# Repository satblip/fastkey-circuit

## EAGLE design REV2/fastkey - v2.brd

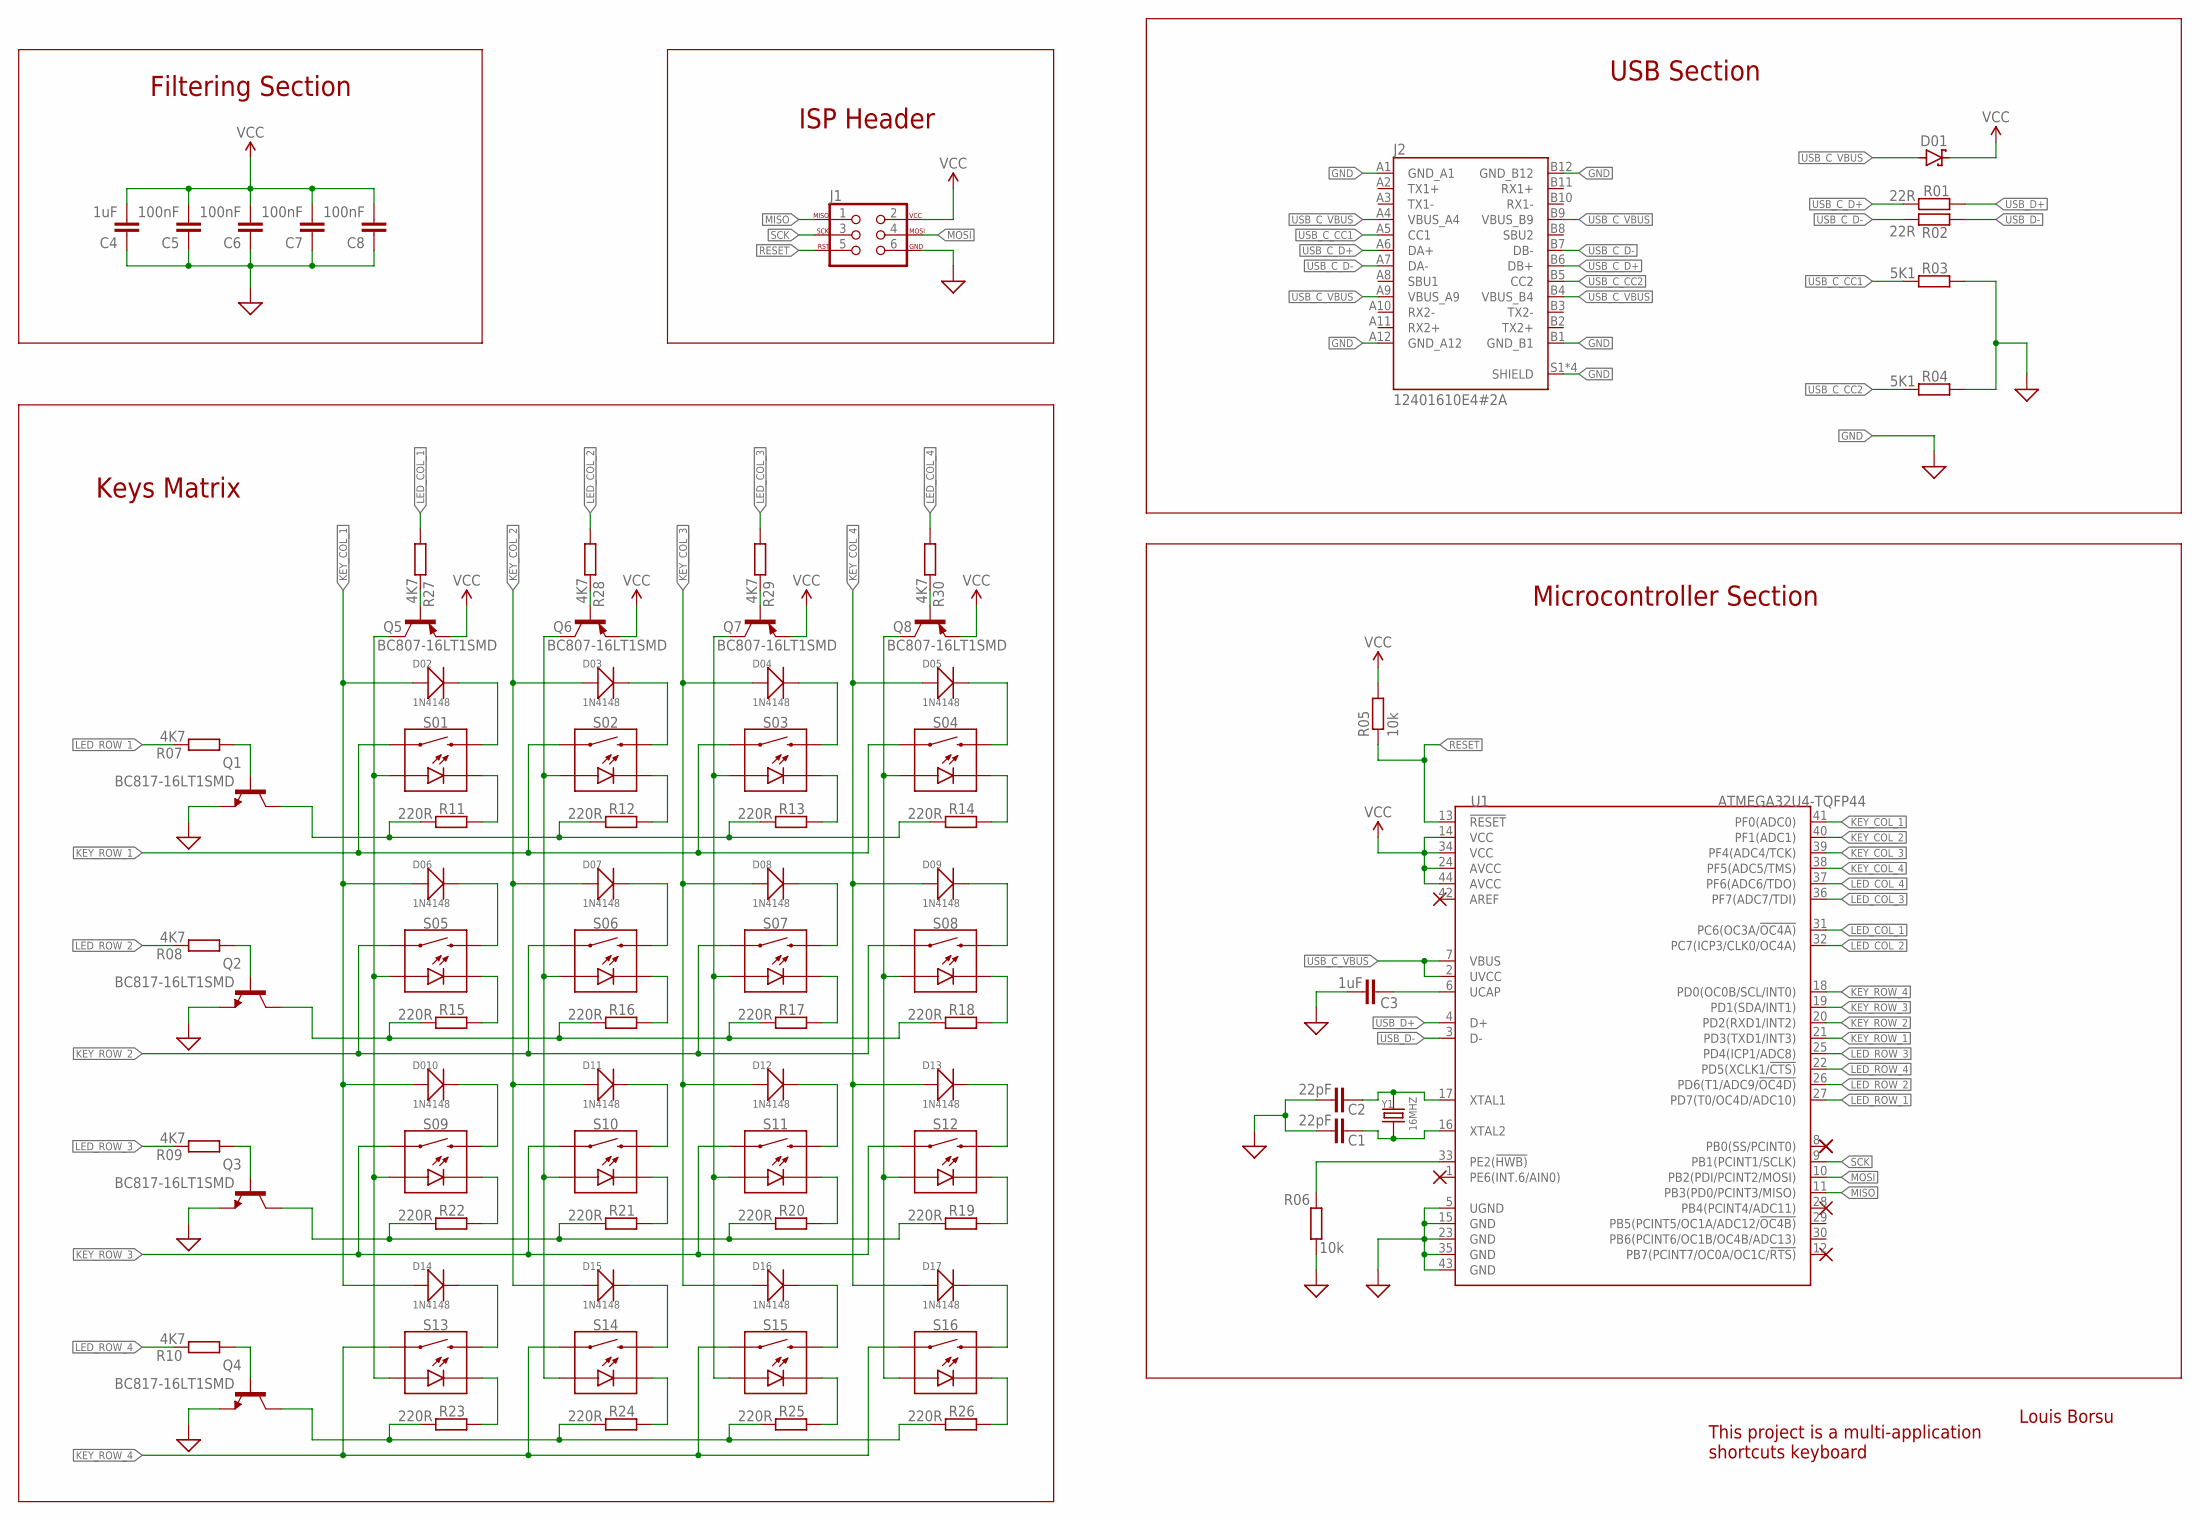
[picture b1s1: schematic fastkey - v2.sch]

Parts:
C1, C2: 22pF; RESC0805_M
C3, C4: 1uF; RESC0805_M
C5, C6, C7, C8: 100nF; RESC0805_M
D01: SCHOTTKY-DIODESMD; SMB
D02, D03, D04, D05, D06, D07, D08, D09, D010, D11, D12, D13, D14, D15, D16, D17: 1N4148; LL-34
J1: AVR_SPI_PROG_3X22X3_LOCK; 2X3_LOCK
J2: 12401610E4#2A; AMPHENOL_12401610E4#2A
Q1, Q2, Q3, Q4: BC817-16LT1SMD; SOT23-BEC
Q5, Q6, Q7, Q8: BC807-16LT1SMD; SOT23-BEC
R01, R02: 22R; R0805
R03, R04: 5K1; R0805
R05, R06: 10k; R0805
R07, R08, R09, R10, R27, R28, R29, R30: 4K7; R0805
R11, R12, R13, R14, R15, R16, R17, R18, R19, R20, R21, R22, R23, R24, R25, R26: 220R; R0805
S01, S02, S03, S04, S05, S06, S07, S08, S09, S10, S11, S12, S13, S14, S15, S16: MOMENTARY-SWITCH-SPST-LED-PTH-CHERRY; CHERRY-MX-LED
U1: ATMEGA32U4-TQFP44; TQFP44-0.8-9.6X9.6MM
Y1: 16MHZ; X2-SMD-5.0X3.2X1.3MM

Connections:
GND: C1.1, C2.1, C3.1, C4.1, C5.1, C6.1, C7.1, C8.1, J1.6, J2.A1 (GND_A1), J2.A12 (GND_A12), J2.B1 (GND_B1), J2.B12 (GND_B12), J2.S1 (SHIELD), J2.S2 (SHIELD), J2.S3 (SHIELD), J2.S4 (SHIELD), Q1.E, Q2.E, Q3.E, Q4.E, R03.1, R04.1, R06.1, U1.5 (UGND), U1.15 (GND), U1.23 (GND), U1.35 (GND), U1.43 (GND)
KEY_COL_1: D02.A (+), D06.A (+), D010.A (+), D14.A (+), U1.41 (PF0(ADC0))
KEY_COL_2: D03.A (+), D07.A (+), D11.A (+), D15.A (+), U1.40 (PF1(ADC1))
KEY_COL_3: D04.A (+), D08.A (+), D12.A (+), D16.A (+), U1.39 (PF4(ADC4/TCK))
KEY_COL_4: D05.A (+), D09.A (+), D13.A (+), D17.A (+), U1.38 (PF5(ADC5/TMS))
KEY_ROW_1: S01.S1 (1), S02.S1 (1), S03.S1 (1), S04.S1 (1), U1.21 (PD3(TXD1/INT3))
KEY_ROW_2: S05.S1 (1), S06.S1 (1), S07.S1 (1), S08.S1 (1), U1.20 (PD2(RXD1/INT2))
KEY_ROW_3: S09.S1 (1), S10.S1 (1), S11.S1 (1), S12.S1 (1), U1.19 (PD1(SDA/INT1))
KEY_ROW_4: S13.S1 (1), S14.S1 (1), S15.S1 (1), S16.S1 (1), U1.18 (PD0(OC0B/SCL/INT0))
LED_COL_1: R27.1, U1.31 (PC6(OC3A/!OC4A))
LED_COL_1_PR: Q5.C, S01.A, S05.A, S09.A, S13.A
LED_COL_2: R28.1, U1.32 (PC7(ICP3/CLK0/OC4A))
LED_COL_2_PR: Q6.C, S02.A, S06.A, S10.A, S14.A
LED_COL_3: R29.1, U1.36 (PF7(ADC7/TDI))
LED_COL_3_PR: Q7.C, S03.A, S07.A, S11.A, S15.A
LED_COL_4: R30.1, U1.37 (PF6(ADC6/TDO))
LED_COL_4_PR: Q8.C, S04.A, S08.A, S12.A, S16.A
LED_ROW_1: R07.2, U1.27 (PD7(T0/OC4D/ADC10))
LED_ROW_1_PR: Q1.C, R11.2, R12.2, R13.2, R14.2
LED_ROW_2: R08.2, U1.26 (PD6(T1/ADC9/!OC4D))
LED_ROW_2_PR: Q2.C, R15.2, R16.2, R17.2, R18.2
LED_ROW_3: R09.2, U1.25 (PD4(ICP1/ADC8))
LED_ROW_3_PR: Q3.C, R19.2, R20.2, R21.2, R22.2
LED_ROW_4: R10.2, U1.22 (PD5(XCLK1/!CTS))
LED_ROW_4_PR: Q4.C, R23.2, R24.2, R25.2, R26.2
MISO: J1.1, U1.11 (PB3(PD0/PCINT3/MISO))
MOSI: J1.4, U1.10 (PB2(PDI/PCINT2/MOSI))
unnamed: C2.2, U1.17 (XTAL1), Y1.2
unnamed: R11.1, S01.K (C)
unnamed: R12.1, S02.K (C)
unnamed: R24.1, S14.K (C)
unnamed: R25.1, S15.K (C)
unnamed: C1.2, U1.16 (XTAL2), Y1.1
unnamed: R26.1, S16.K (C)
unnamed: R19.1, S12.K (C)
unnamed: R20.1, S11.K (C)
unnamed: R21.1, S10.K (C)
unnamed: D02.C (-), S01.S2 (2)
unnamed: R22.1, S09.K (C)
unnamed: R15.1, S05.K (C)
unnamed: R16.1, S06.K (C)
unnamed: R17.1, S07.K (C)
unnamed: R18.1, S08.K (C)
unnamed: R14.1, S04.K (C)
unnamed: R13.1, S03.K (C)
unnamed: Q1.B, R07.1
unnamed: Q2.B, R08.1
unnamed: C3.2, U1.6 (UCAP)
unnamed: R06.2, U1.33 (PE2(!HWB))
unnamed: Q5.B, R27.2
unnamed: Q6.B, R28.2
unnamed: Q7.B, R29.2
unnamed: D04.C (-), S03.S2 (2)
unnamed: Q8.B, R30.2
unnamed: Q3.B, R09.1
unnamed: R23.1, S13.K (C)
unnamed: Q4.B, R10.1
unnamed: D03.C (-), S02.S2 (2)
unnamed: D05.C (-), S04.S2 (2)
unnamed: D06.C (-), S05.S2 (2)
unnamed: D07.C (-), S06.S2 (2)
unnamed: D08.C (-), S07.S2 (2)
unnamed: D09.C (-), S08.S2 (2)
unnamed: D010.C (-), S09.S2 (2)
unnamed: D11.C (-), S10.S2 (2)
unnamed: D15.C (-), S14.S2 (2)
unnamed: D12.C (-), S11.S2 (2)
unnamed: D14.C (-), S13.S2 (2)
unnamed: D16.C (-), S15.S2 (2)
unnamed: D13.C (-), S12.S2 (2)
unnamed: D17.C (-), S16.S2 (2)
RESET: J1.5, R05.1, U1.13 (!RESET)
SCK: J1.3, U1.9 (PB1(PCINT1/SCLK))
USB_C_CC1: J2.A5 (CC1), R03.2
USB_C_CC2: J2.B5 (CC2), R04.2
USB_C_D+: J2.A6 (DA+), J2.B6 (DB+), R01.2
USB_C_D-: J2.A7 (DA-), J2.B7 (DB-), R02.2
USB_C_VBUS: D01.A, J2.A4 (VBUS_A4), J2.A9 (VBUS_A9), J2.B4 (VBUS_B4), J2.B9 (VBUS_B9), U1.2 (UVCC), U1.7 (VBUS)
USB_D+: R01.1, U1.4 (D+)
USB_D-: R02.1, U1.3 (D-)
VCC: C4.2, C5.2, C6.2, C7.2, C8.2, D01.C, J1.2, Q5.E, Q6.E, Q7.E, Q8.E, R05.2, U1.14 (VCC), U1.24 (AVCC), U1.34 (VCC), U1.44 (AVCC)

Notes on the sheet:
Keys Matrix
Microcontroller Section
Filtering Section
USB Section
ISP Header
This project is a multi-application shortcuts keyboard
Louis Borsu

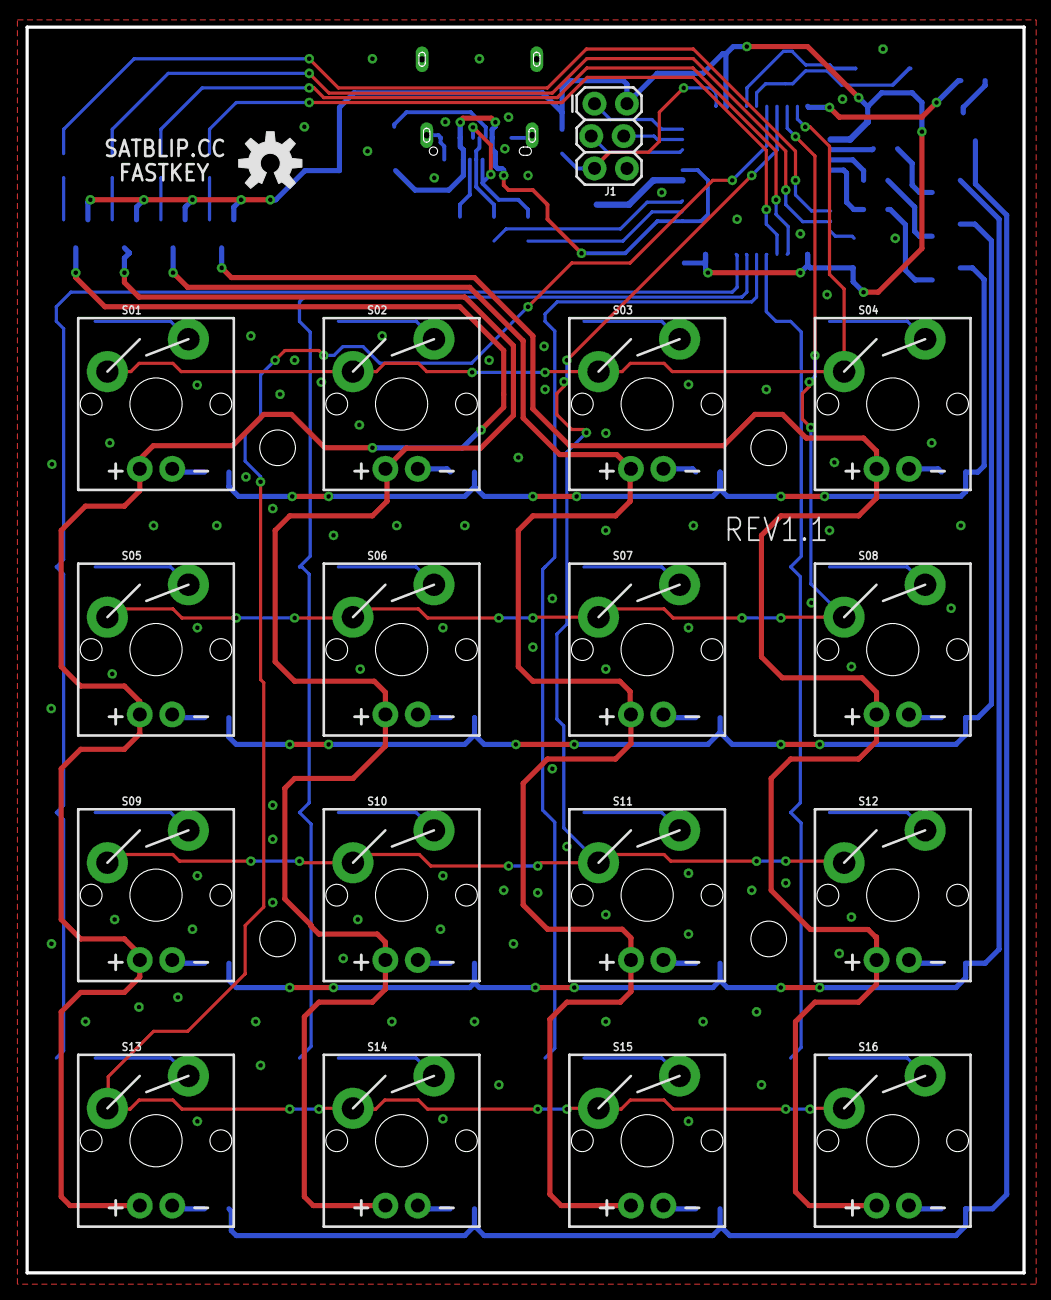
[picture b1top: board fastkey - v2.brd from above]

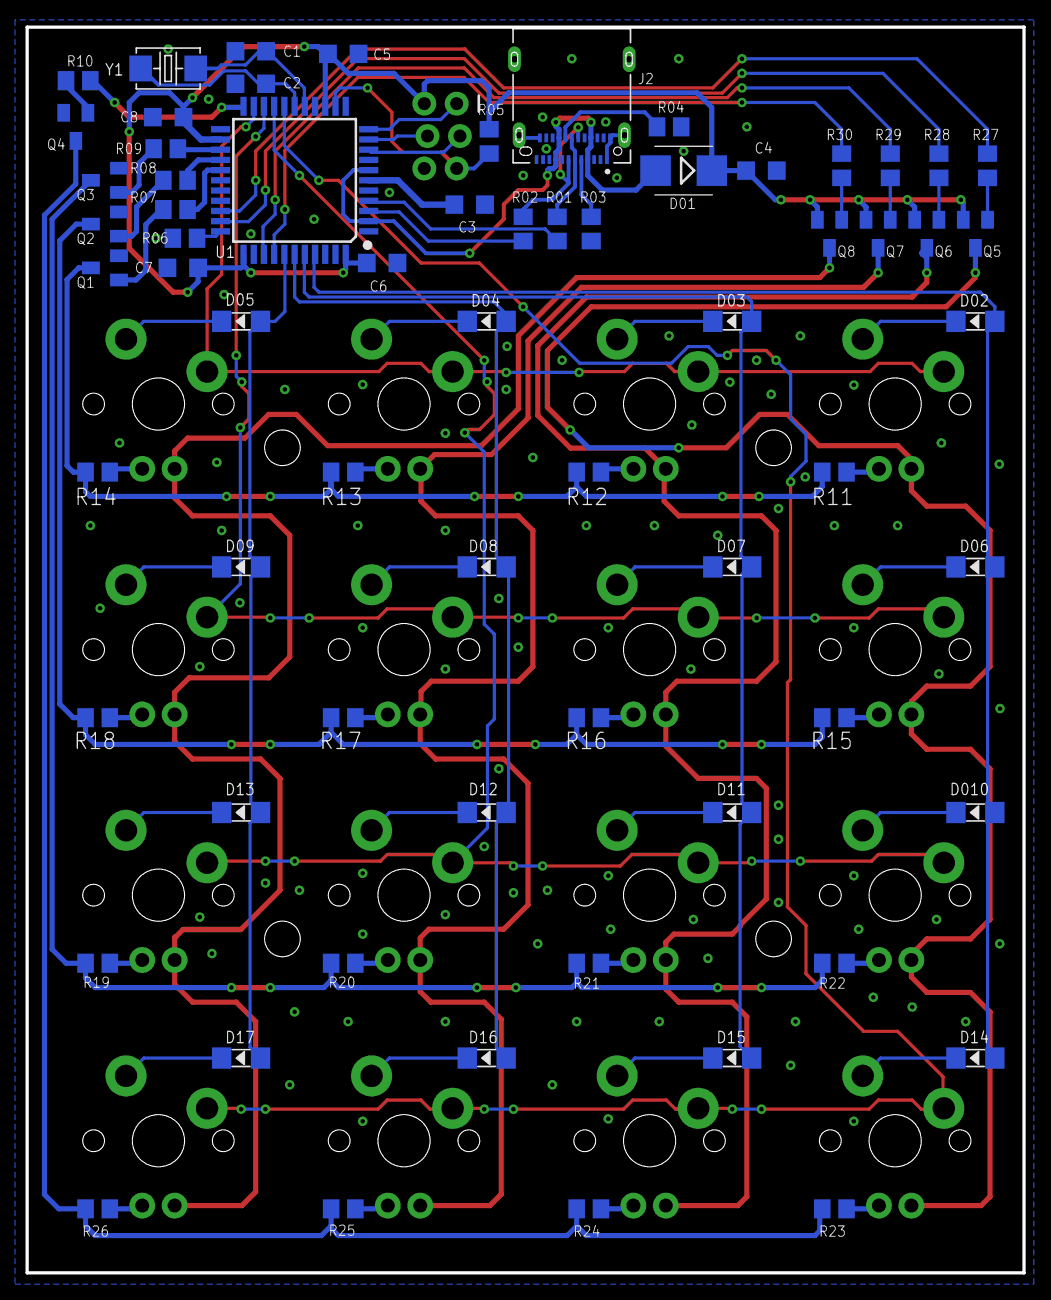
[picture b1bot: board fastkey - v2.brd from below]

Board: 2 copper layers, 78.1 x 97.6 mm, 84 parts (66 on the bottom side), 81 nets.

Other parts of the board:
U$1: OSHW-LOGO-M

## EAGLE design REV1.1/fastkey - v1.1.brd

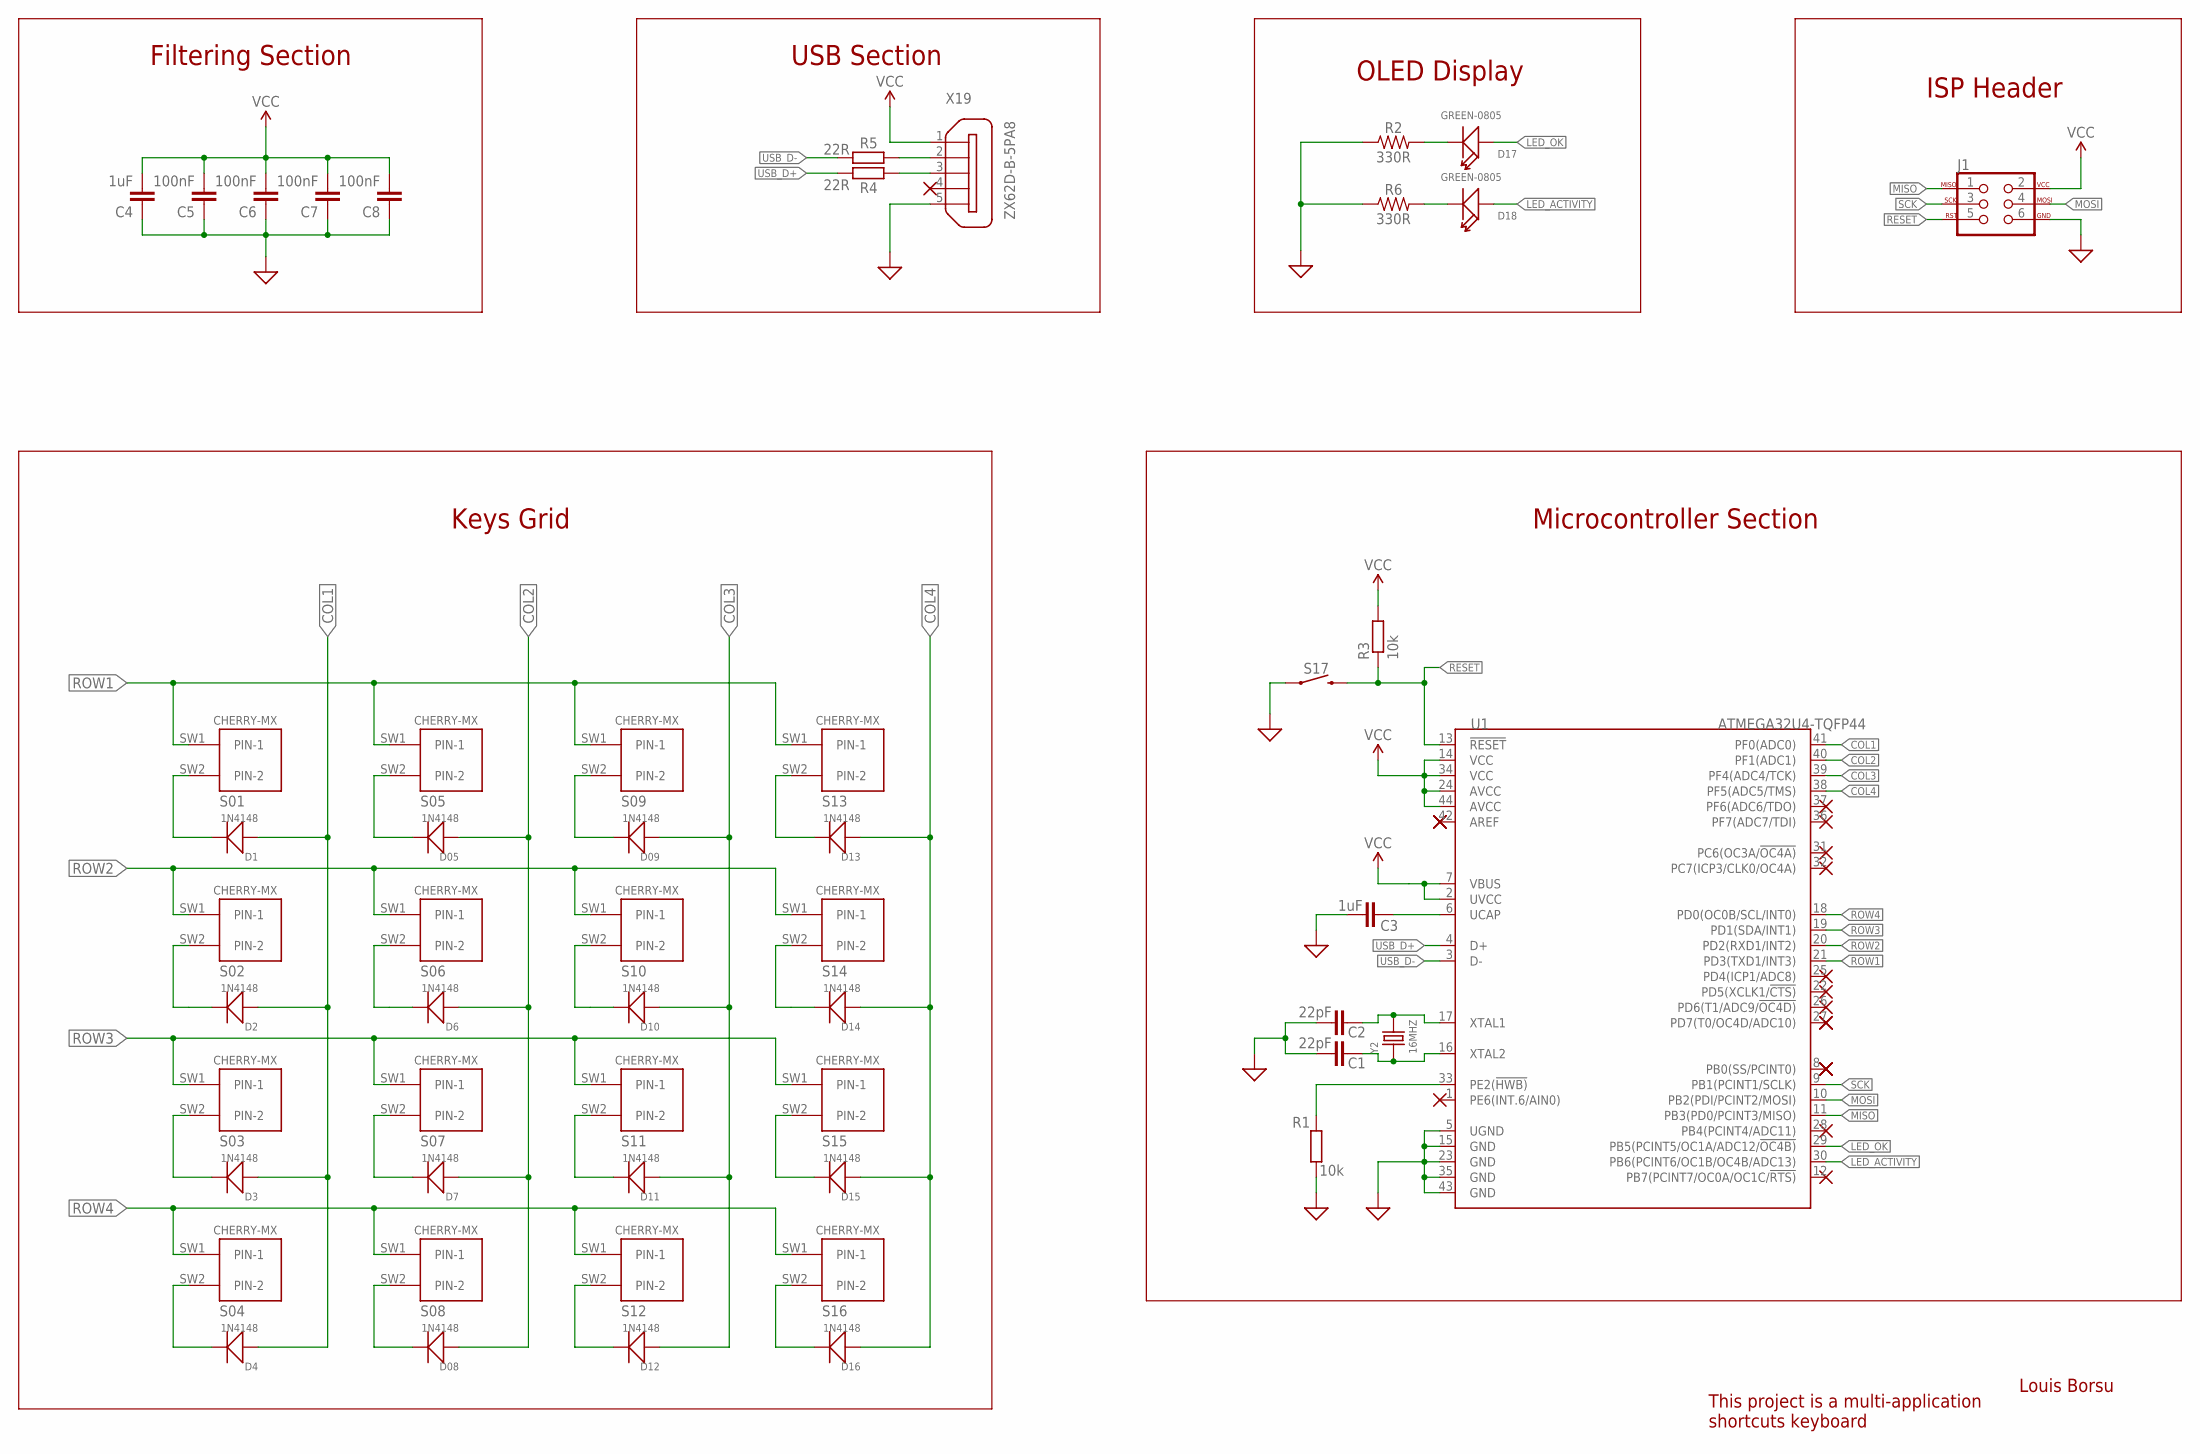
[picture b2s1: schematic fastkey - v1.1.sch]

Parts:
C1, C2: 22pF; RESC0805_M
C3, C4: 1uF; RESC0805_M
C5, C6, C7, C8: 100nF; RESC0805_M
D1, D2, D3, D4, D05, D6, D7, D08, D09, D10, D11, D12, D13, D14, D15, D16: 1N4148; LL-34
D17, D18: GREEN-0805; LED-0805
J1: AVR_SPI_PROG_3X22X3_LOCK; 2X3_LOCK
R1, R3: 10k; R0805
R2, R6: 330R; 0805
R4, R5: 22R; R0805
S01, S02, S03, S04, S05, S06, S07, S08, S09, S10, S11, S12, S13, S14, S15, S16: CHERRY-MX
S17: MOMENTARY-SWITCH-SPST-SMD-6.2MM-TALL; TACTILE_SWITCH_SMD_6.2MM_TALL
U1: ATMEGA32U4-TQFP44; TQFP44-0.8-9.6X9.6MM
X19: ZX62D-B-5PA8
Y2: 16MHZ; X2-SMD-5.0X3.2X1.3MM

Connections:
COL1: D1.A (+), D2.A (+), D3.A (+), D4.A (+), U1.41 (PF0(ADC0))
COL2: D05.A (+), D6.A (+), D7.A (+), D08.A (+), U1.40 (PF1(ADC1))
COL3: D09.A (+), D10.A (+), D11.A (+), D12.A (+), U1.39 (PF4(ADC4/TCK))
COL4: D13.A (+), D14.A (+), D15.A (+), D16.A (+), U1.38 (PF5(ADC5/TMS))
GND: C1.1, C2.1, C3.1, C4.1, C5.1, C6.1, C7.1, C8.1, J1.6, R1.1, R2.1, R6.1, S17.A2 (1), U1.5 (UGND), U1.15 (GND), U1.23 (GND), U1.35 (GND), U1.43 (GND), X19.5
LED_ACTIVITY: D18.+, U1.30 (PB6(PCINT6/OC1B/OC4B/ADC13))
LED_OK: D17.+, U1.29 (PB5(PCINT5/OC1A/ADC12/!OC4B))
MISO: J1.1, U1.11 (PB3(PD0/PCINT3/MISO))
MOSI: J1.4, U1.10 (PB2(PDI/PCINT2/MOSI))
unnamed: C2.2, U1.17 (XTAL1), Y2.2
unnamed: D4.C (-), S04.SW2 (PIN-2)
unnamed: D3.C (-), S03.SW2 (PIN-2)
unnamed: D2.C (-), S02.SW2 (PIN-2)
unnamed: D1.C (-), S01.SW2 (PIN-2)
unnamed: C1.2, U1.16 (XTAL2), Y2.1
unnamed: D08.C (-), S08.SW2 (PIN-2)
unnamed: D7.C (-), S07.SW2 (PIN-2)
unnamed: D6.C (-), S06.SW2 (PIN-2)
unnamed: D05.C (-), S05.SW2 (PIN-2)
unnamed: D18.-, R6.2
unnamed: D12.C (-), S12.SW2 (PIN-2)
unnamed: D11.C (-), S11.SW2 (PIN-2)
unnamed: D10.C (-), S10.SW2 (PIN-2)
unnamed: D09.C (-), S09.SW2 (PIN-2)
unnamed: D17.-, R2.2
unnamed: D16.C (-), S16.SW2 (PIN-2)
unnamed: D15.C (-), S15.SW2 (PIN-2)
unnamed: D14.C (-), S14.SW2 (PIN-2)
unnamed: D13.C (-), S13.SW2 (PIN-2)
unnamed: C3.2, U1.6 (UCAP)
unnamed: R1.2, U1.33 (PE2(!HWB))
unnamed: R5.1, X19.2
unnamed: R4.1, X19.3
RESET: J1.5, R3.1, S17.B2 (2), U1.13 (!RESET)
ROW1: S01.SW1 (PIN-1), S05.SW1 (PIN-1), S09.SW1 (PIN-1), S13.SW1 (PIN-1), U1.21 (PD3(TXD1/INT3))
ROW2: S02.SW1 (PIN-1), S06.SW1 (PIN-1), S10.SW1 (PIN-1), S14.SW1 (PIN-1), U1.20 (PD2(RXD1/INT2))
ROW3: S03.SW1 (PIN-1), S07.SW1 (PIN-1), S11.SW1 (PIN-1), S15.SW1 (PIN-1), U1.19 (PD1(SDA/INT1))
ROW4: S04.SW1 (PIN-1), S08.SW1 (PIN-1), S12.SW1 (PIN-1), S16.SW1 (PIN-1), U1.18 (PD0(OC0B/SCL/INT0))
SCK: J1.3, U1.9 (PB1(PCINT1/SCLK))
USB_D+: R4.2, U1.4 (D+)
USB_D-: R5.2, U1.3 (D-)
VCC: C4.2, C5.2, C6.2, C7.2, C8.2, J1.2, R3.2, U1.2 (UVCC), U1.7 (VBUS), U1.14 (VCC), U1.24 (AVCC), U1.34 (VCC), U1.44 (AVCC), X19.1

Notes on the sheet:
Keys Grid
Microcontroller Section
Filtering Section
USB Section
OLED Display
ISP Header
This project is a multi-application shortcuts keyboard
Louis Borsu

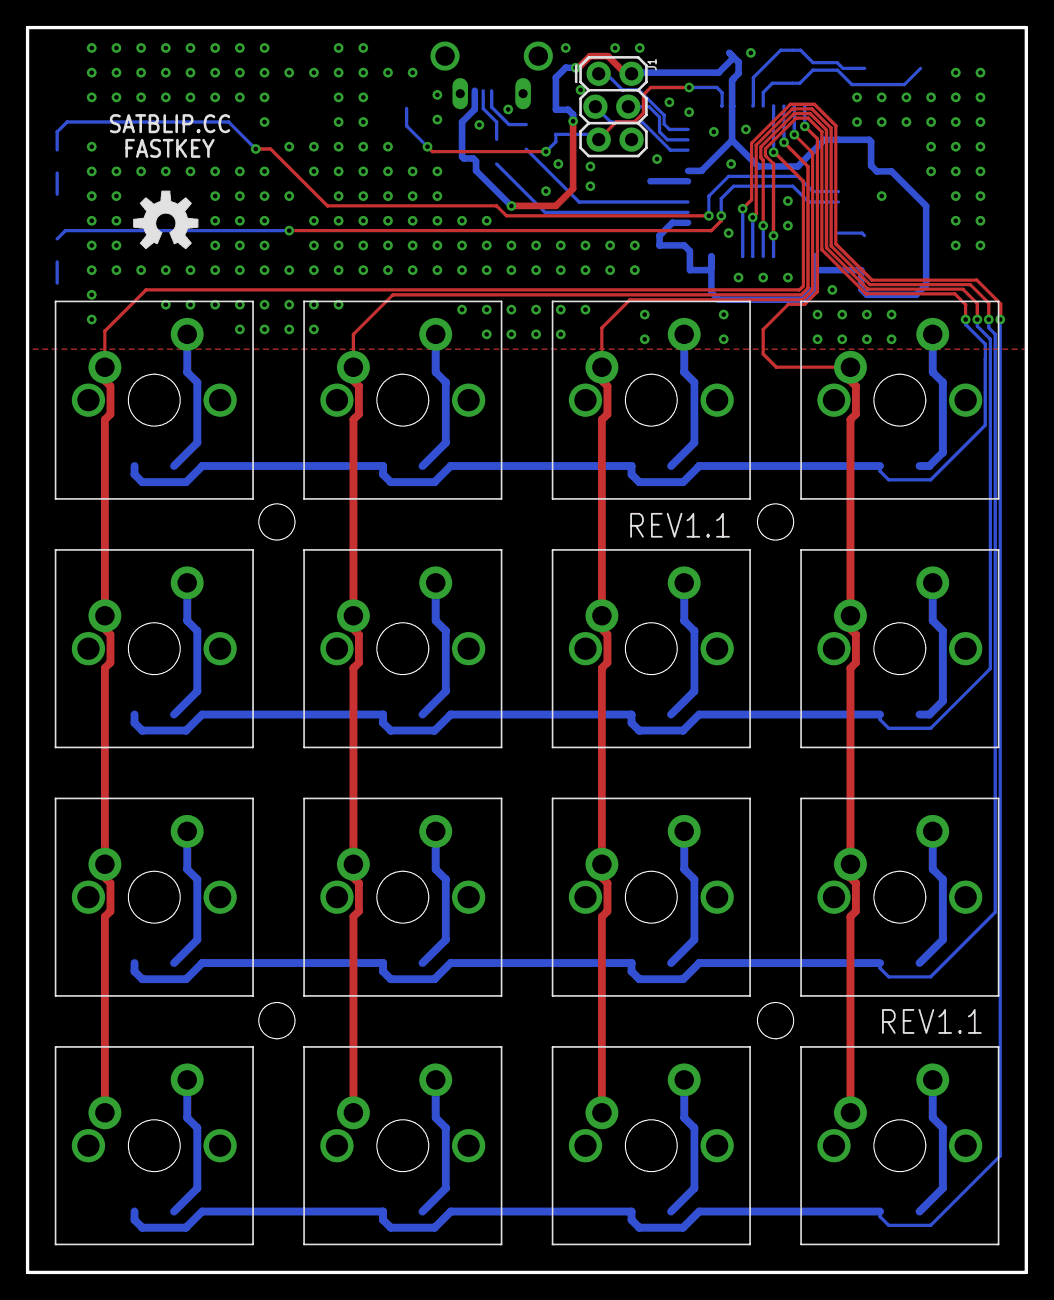
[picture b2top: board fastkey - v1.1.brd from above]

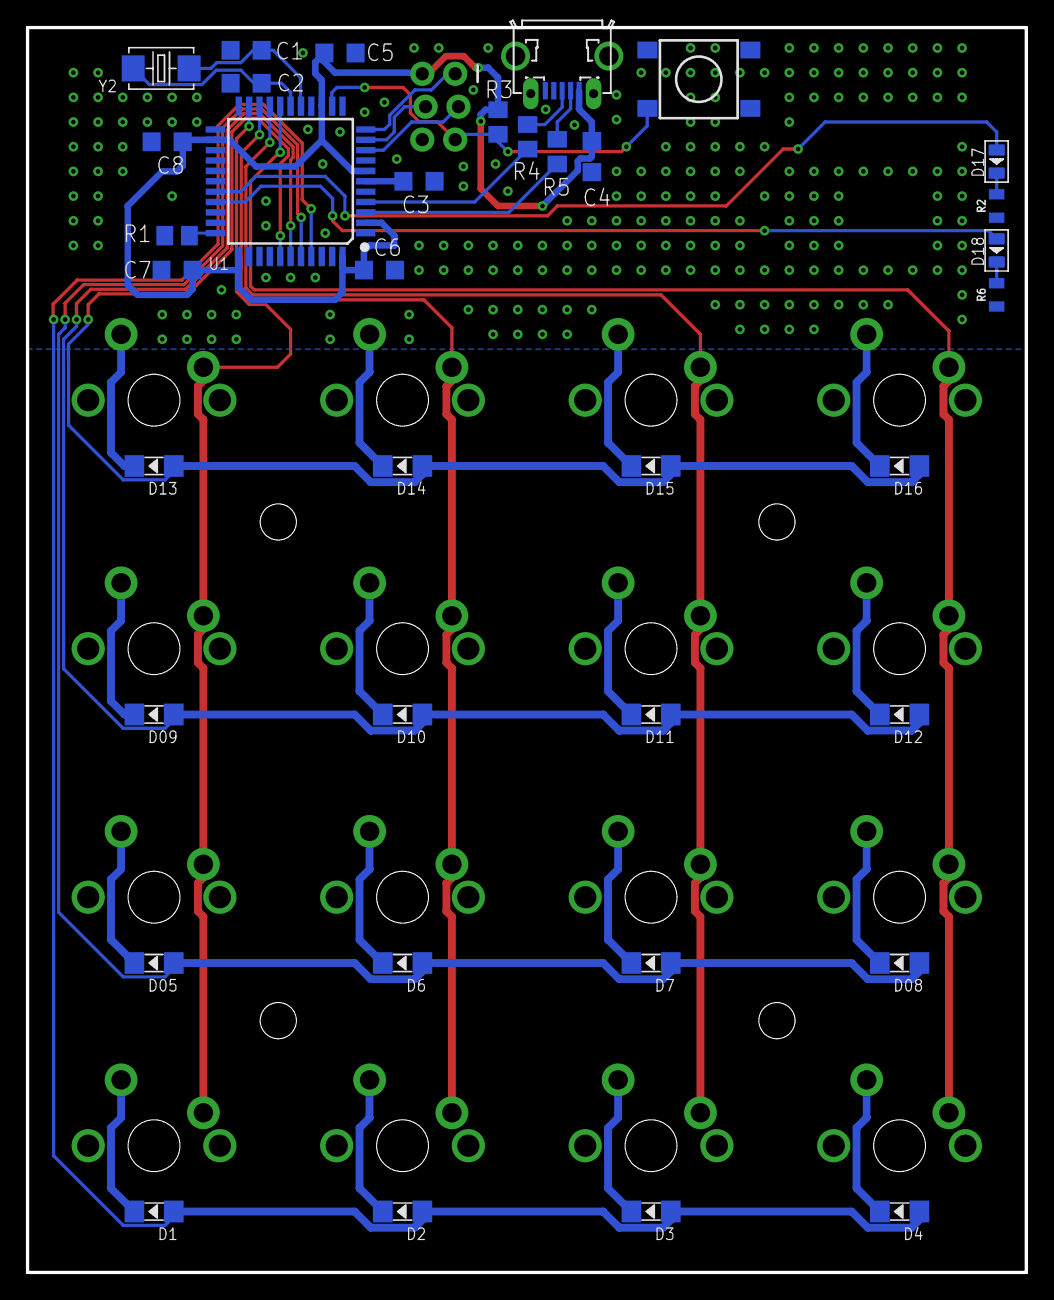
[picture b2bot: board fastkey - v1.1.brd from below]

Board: 2 copper layers, 77.1 x 96.1 mm, 54 parts (36 on the bottom side), 42 nets.

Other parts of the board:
U$1: OSHW-LOGO-M

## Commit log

2018-10-27 init(initial): first commit
2018-12-23 feat(rev1.1): update to rev 1.1
2019-08-30 feat(2.0): adding design file for version 2.0
2019-08-30 Create LICENSE

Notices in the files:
parts and their libraries:
SparkFun-Connectors: Licensing: Creative Commons ShareAlike 4.0 International - https://creativecommons.org/licenses/by-sa/4.0
